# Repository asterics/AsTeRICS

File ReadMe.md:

# Welcome to AsTeRICS
-------------------

AsTeRICS is a free and Open-Source graphical construction set for assistive technologies (AT).
It allows the creation of flexible solutions for people with disabilities using a large set of sensors and actuators.

Possible applications are  
* Computer input (mouse, keyboard, joystick)
* Environmental Control (KNX, FS20, IR, EnOcean, openHAB)
* Toys and Games (Playstation 3, computer games, RC-toys ...)
* Brain/Neural computer interfaces (Enobio, OpenVIBE, OpenEEG)
* Android Phone support (SMS, calls)
* and many more!

For more information see our website http://www.asterics.eu.

## Demos (Solutions)
Check out some solutions [here](https://www.asterics.eu/solutions/)

## Quick Build Instructions
To clone and compile the AsTeRICS framework, please execute the following steps:

1. Clone Repository (submodules will be cloned during build)
  ```
  git clone https://github.com/asterics/AsTeRICS.git
  ```
2. Install the [**Java Development Kit (JDK, 32bit preferred) = 8**](http://www.oracle.com/technetwork/java/javase/downloads/index.html)
  * Ensure to set ```JAVA_HOME``` to the folder where you installed the Java JDK and add the JDK bin path to the  Environment Variable ```Path```
3. [apache ant build framework (version >= 1.9.1)](http://ant.apache.org/bindownload.cgi)
  * Ensure to set ```ANT_HOME``` to the folder where you installed ant and add the ant bin path to the Environment Variable ```Path```
  * The ```git``` command line tool must be available from within ant, ensure to set the Environment Variable ```Path``` to the respective ```bin``` folder.
4. Open a terminal and start the AsTeRICS Runtime Environment (ARE) by calling:

  ```
  ant run
  ```
  
 If you don't need commandline support, you can use an IDE for Java Developers, e.g. [Eclipse](http://www.eclipse.org/downloads/packages/eclipse-ide-java-developers/neon3), which already contains ant. There you can directly execute ant targets by selecting the build file ```build.xml``` and select the target of choice, e.g. ```run```.
 
## Documentation

* [AsTeRICS Tutorial with screencasts](https://ds.gpii.net/learn/tutorials/integration-alternative-input-modalities)
* [Getting Started](https://www.asterics.eu/get-started/)
* [Tutorials](https://www.asterics.eu/customize/)
* [Developer Manual](https://www.asterics.eu/develop/)
* [Plugin Hellp](https://www.asterics.eu/plugins/)

You can find more documentation and build plans for some hardware devices in [ModelGuides](https://github.com/asterics/AsTeRICS/tree/master/Documentation/ModelGuides) and  [DIYGuides](https://github.com/asterics/AsTeRICS/tree/master/Documentation/DIYGuides).

## Contact

If you want to contribute to the AsTeRICS project, have questions or just need help using it don't bother to create an [issue](https://github.com/asterics/AsTeRICS/issues), pull request or via the [contact page](https://www.asterics.eu/get-involved/Contact.html).  

If you want to support the development of AsTeRICS you're very welcome to donate to the AsTeRICS Foundation:

<div>

<span>&nbsp;&nbsp;&nbsp;</span>

</div>

## License

This project has been partly funded by the European Commission,  Grant Agreement Number 247730 in the years 2010-2012.
Since 2013, further development of AsTeRICS software and hardware components is hosted at:  https://github.com/asterics/AsTeRICS

#### ACS and NativeASAPI libraries
Licensed under [LGPL](http://www.gnu.org/licenses/lgpl.html)

#### ARE-middleware, ARE-plugins, services and BNCI Suite
Licensed under a dual license [MIT or GPL with CLASSPATH exception](ARE-LICENSE_MITOrGPLv3WithException.txt)

##### How to apply the dual licensing

You may use these components under the terms of the MIT License, if no source code (plugins, services, libraries, ...) which is contained in your desired collection of ARE plugins and services is licensed under the GNU General Public License (GPL).
In order for that, you can remove unneeded plugins or services.

**Please note:** There are also some plugins (e.g. MathEvaluator, VLC) which are **GPL without CLASSPATH** exception, so in this case your license would have to be **GPL** as well.

Please have a look at the individual licenses of the AsTeRICS plugins and services. You find the license files in the subfolder LICENSE of every plugin.

## Disclaimer

This software is provided 'as-is', without any express or implied warranty. 
In no event will the authors be held liable for any damages arising from the use of this software. See [DISCLAIMER](DISCLAIMER.TXT)

## Releases

* See [CHANGELOG](./CHANGELOG.md) or old [Release Notes](RELEASE_NOTES.md) and the published [releases](https://github.com/asterics/AsTeRICS/releases)

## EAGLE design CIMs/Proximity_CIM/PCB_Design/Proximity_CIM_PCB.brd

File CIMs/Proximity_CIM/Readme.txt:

AsTeRICS proximity CIM, FHTW

The firmware fits for the Atmel AVR AT90USB1286 microcontroller 
(e.g. mounted on the "teensy++" board, see http://www.pjrc.com/store/teensypp.html)

The proximity CIM provides a distance measurement curcuit based upun a CNY-70 infrared object detection sensor.
It can be used a assistive input device for persons to select / control via small movement e.g. of a finger or of the chin.

Important files/folders:
  ProximityCIM.aps:  project file, can be opened/built with AVRStudio 4 + WinAVR
  ProximityCIM.hex:  binary/executable, can be downloaded via Atmel FLIP into the microcontroller
  subfolder "PCB_Design": schematics/layout files for a PCB conaining microcontroller and circuits for the proximity detetor

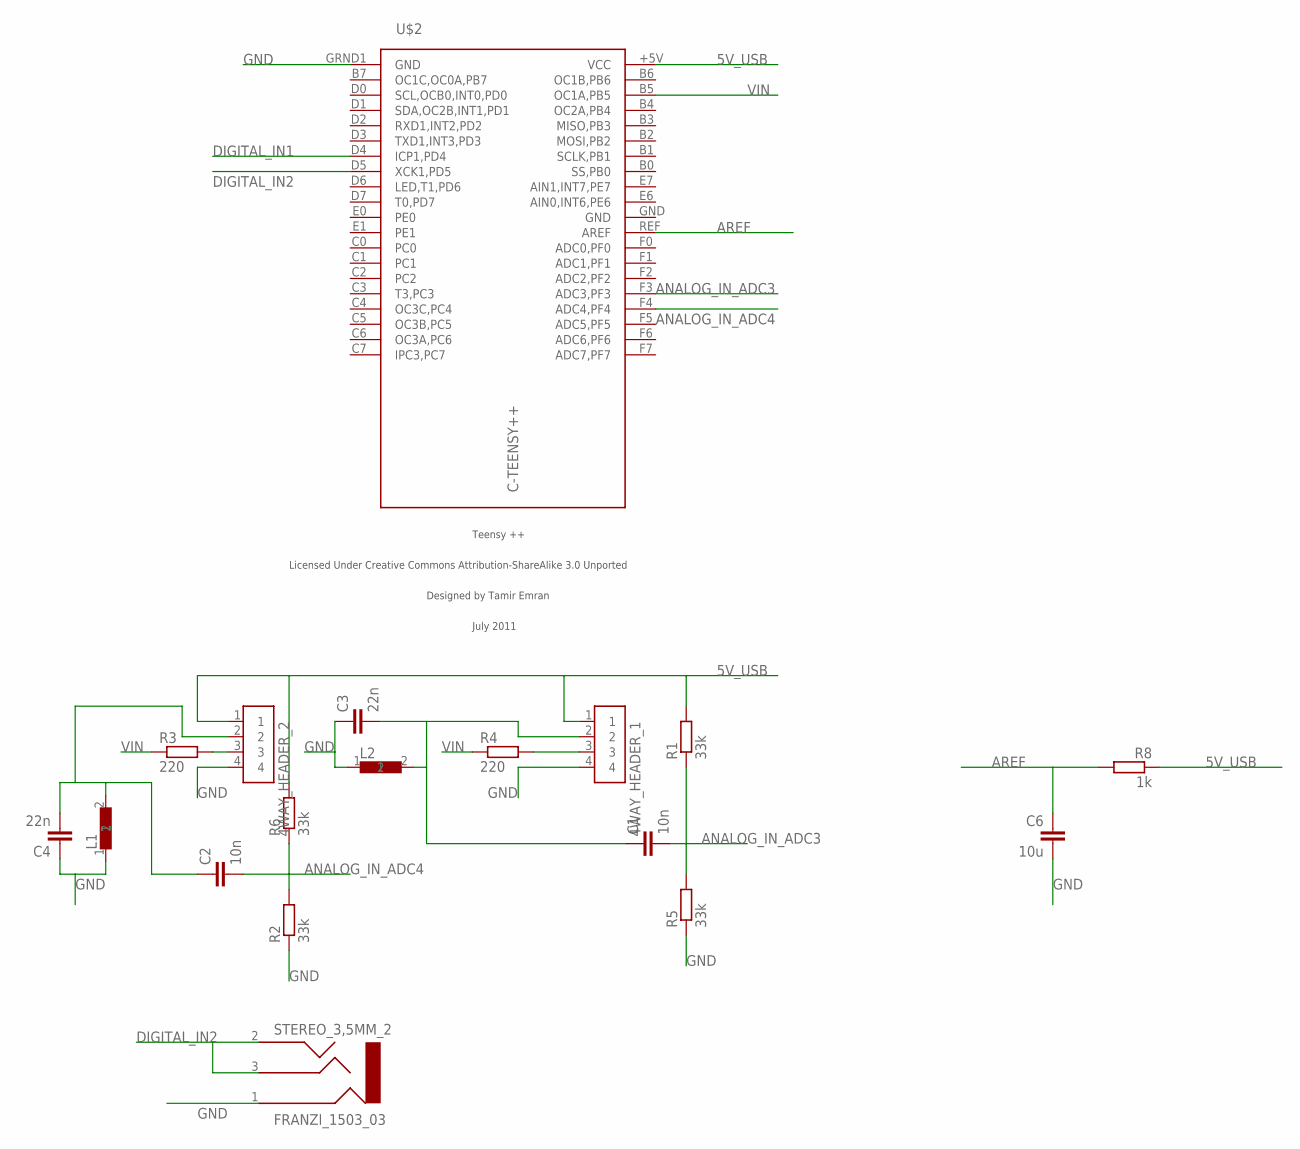
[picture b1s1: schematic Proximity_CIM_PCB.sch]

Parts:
4WAY_HEADER_1, 4WAY_HEADER_2: 4WAY_HEADER
C1, C2: 10n; C0805
C3, C4: 22n; C1206
C6: 10u; C0805
L1, L2: INDUCTOR_1
R1, R2, R5, R6: 33k; R0805
R3, R4: 220; R0805
R8: 1k; R0805
STEREO_3,5MM_2: FRANZI_1503_03; 1503_03
U$2: C-TEENSY++; TEENSY++

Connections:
5V_USB: 4WAY_HEADER_1.1, 4WAY_HEADER_2.1, R1.2, R6.2, R8.1, U$2.+5V (VCC)
ANALOG_IN_ADC3: C1.2, R1.1, R5.2, U$2.F3 (ADC3,PF3)
ANALOG_IN_ADC4: C2.2, R2.2, R6.1, U$2.F4 (ADC4,PF4)
AREF: C6.1, R8.2, U$2.REF (AREF)
DIGITAL_IN1: U$2.D4 (ICP1,PD4)
DIGITAL_IN2: STEREO_3,5MM_2.2, STEREO_3,5MM_2.3, U$2.D5 (XCK1,PD5)
GND: 4WAY_HEADER_1.4, 4WAY_HEADER_2.4, C3.1, C4.1, C6.2, L1.1, L2.1, R2.1, R5.1, STEREO_3,5MM_2.1, U$2.GND, U$2.GRND1 (GND)
unnamed: 4WAY_HEADER_1.3, R4.2
unnamed: 4WAY_HEADER_1.2, C1.1, C3.2, L2.2
unnamed: 4WAY_HEADER_2.2, C2.1, C4.2, L1.2
unnamed: 4WAY_HEADER_2.3, R3.2
VIN: R3.1, R4.1, U$2.B5 (OC1A,PB5)

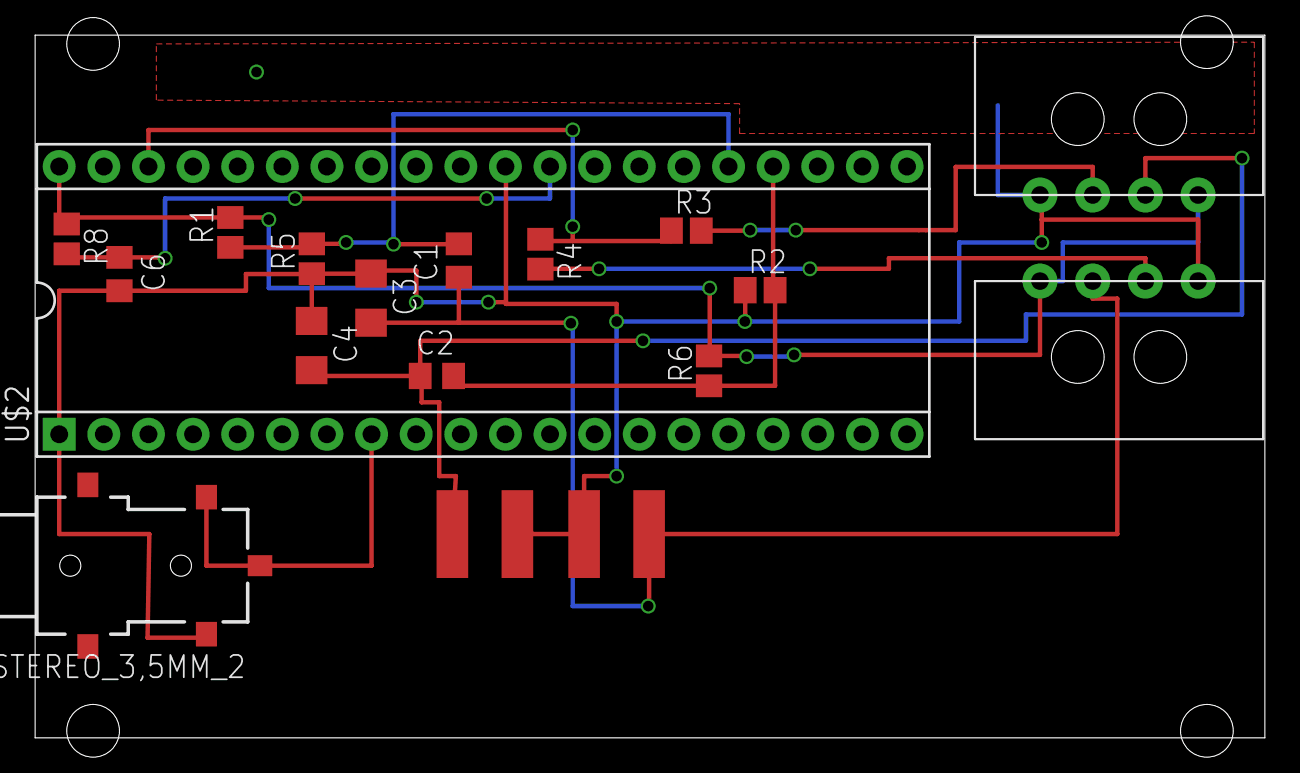
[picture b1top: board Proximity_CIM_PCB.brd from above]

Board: 2 copper layers, 70.0 x 40.0 mm, 18 parts (0 on the bottom side), 11 nets.

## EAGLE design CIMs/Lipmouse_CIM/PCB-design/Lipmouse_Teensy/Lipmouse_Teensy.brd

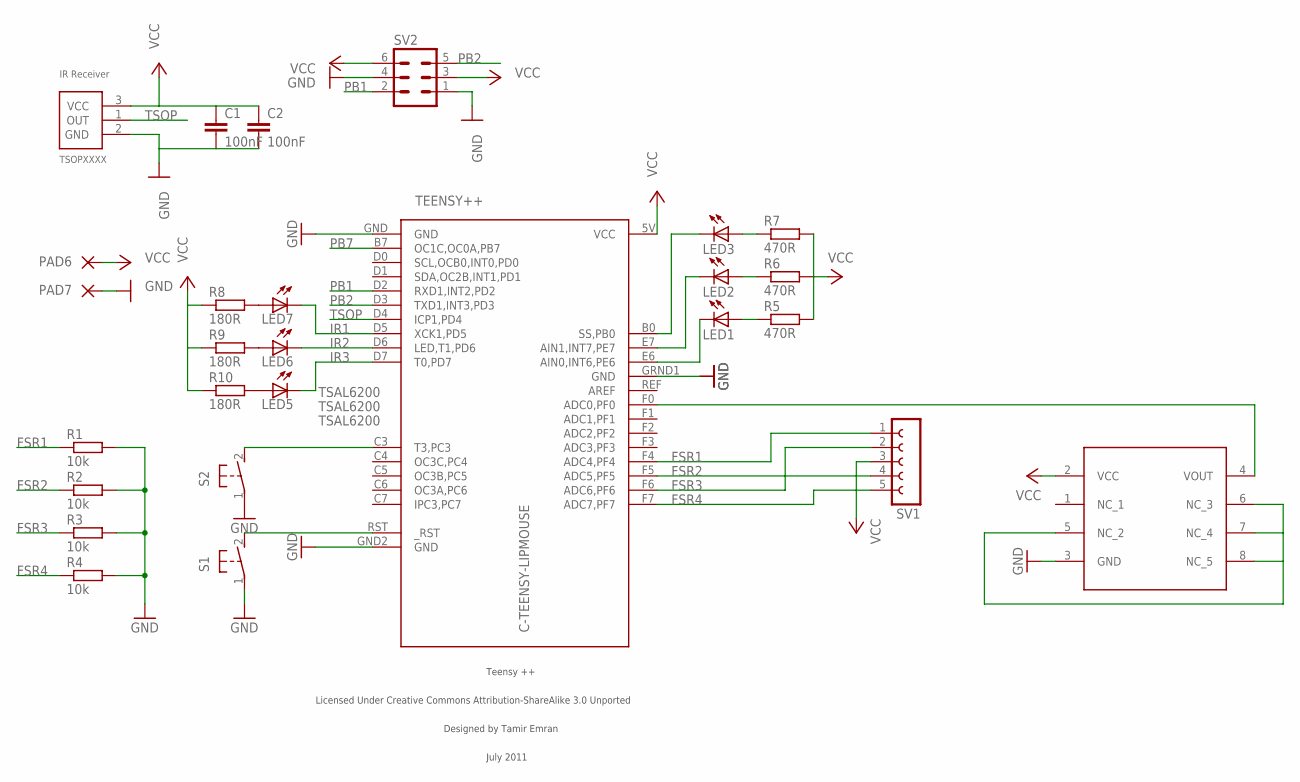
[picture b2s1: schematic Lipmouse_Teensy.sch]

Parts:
C1, C2: 100nF; C0805K
LED1, LED2, LED3: LED3MM
LED5, LED6, LED7: TSAL6200; LED5MM
PAD6, PAD7: 1,6/0,9
R1, R2, R3, R4: 10k; R0805W
R5, R6, R7: 470R; R0805W
R8, R9, R10: 180R; R0805W
S1, S2: 31-XX; B3F-31XX
SV1: FE05-1
SV2: ML6
TEENSY++: C-TEENSY-LIPMOUSE; TEENSY++
U$2: MP3V7007GP; SMP_MP3V7007
U$3: TSOP4838; TSOP2XXX

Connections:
FSR1: R1.1, SV1.1, TEENSY++.F4 (ADC4,PF4)
FSR2: R2.1, SV1.4, TEENSY++.F5 (ADC5,PF5)
FSR3: R3.1, SV1.2, TEENSY++.F6 (ADC6,PF6)
FSR4: R4.1, SV1.5, TEENSY++.F7 (ADC7,PF7)
GND: C1.2, C2.2, PAD7.1, R1.2, R2.2, R3.2, R4.2, S1.1, S2.1, SV2.1, SV2.4, TEENSY++.GND, TEENSY++.GND2 (GND), TEENSY++.GRND1 (GND), U$2.3 (GND), U$3.2 (GND)
IR1: LED7.K (C), TEENSY++.D5 (XCK1,PD5)
IR2: LED6.K (C), TEENSY++.D6 (LED,T1,PD6)
IR3: LED5.K (C), TEENSY++.D7 (T0,PD7)
unnamed: LED1.A, R5.1
unnamed: LED2.A, R6.1
unnamed: LED3.A, R7.1
unnamed: S2.2 (S), TEENSY++.C3 (T3,PC3)
unnamed: LED1.K (C), TEENSY++.E6 (AIN0,INT6,PE6)
unnamed: TEENSY++.F0 (ADC0,PF0), U$2.4 (VOUT)
unnamed: LED2.K (C), TEENSY++.E7 (AIN1,INT7,PE7)
unnamed: LED3.K (C), TEENSY++.B0 (SS,PB0)
unnamed: LED7.A, R8.2
unnamed: LED6.A, R9.2
unnamed: LED5.A, R10.2
unnamed: U$2.5 (NC_2), U$2.6 (NC_3), U$2.7 (NC_4), U$2.8 (NC_5)
unnamed: S1.2 (S), TEENSY++.RST (_RST)
PB1: SV2.2, TEENSY++.D2 (RXD1,INT2,PD2)
PB2: SV2.5, TEENSY++.D3 (TXD1,INT3,PD3)
PB7: TEENSY++.B7 (OC1C,OC0A,PB7)
TSOP: TEENSY++.D4 (ICP1,PD4), U$3.1 (OUT)
VCC: C1.1, C2.1, PAD6.1, R5.2, R6.2, R7.2, R8.1, R9.1, R10.1, SV1.3, SV2.3, SV2.6, TEENSY++.5V (VCC), U$2.2 (VCC), U$3.3 (VCC)

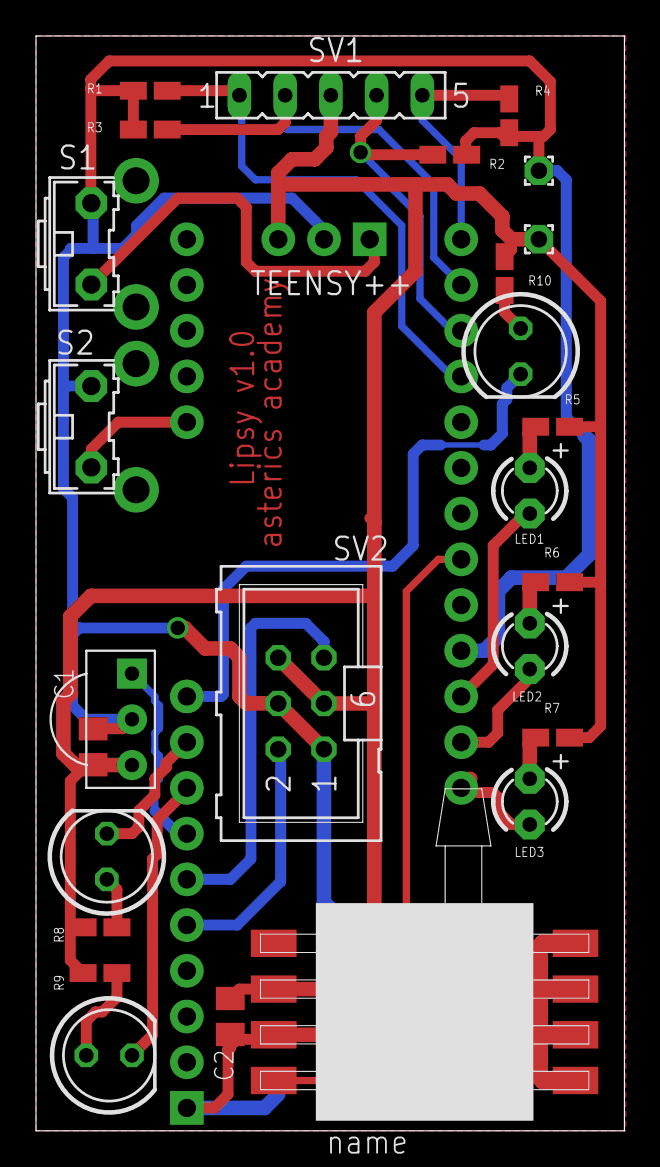
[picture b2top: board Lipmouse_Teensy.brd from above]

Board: 2 copper layers, 32.7 x 60.8 mm, 27 parts (1 on the bottom side), 25 nets.

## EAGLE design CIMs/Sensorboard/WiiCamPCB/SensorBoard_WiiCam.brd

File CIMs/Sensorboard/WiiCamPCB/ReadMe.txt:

AsTeRICs Sensorboard Printed Circuit Board design files

This folder contains the EageCad Design Files for the Sensorboard - version which supports the Optical Sensor of the Wiimote (via I2C interface)
Please refer to the SmartVisionModule DIY guide (documentation/DIYGuides/SmartVisionModule) for more details.

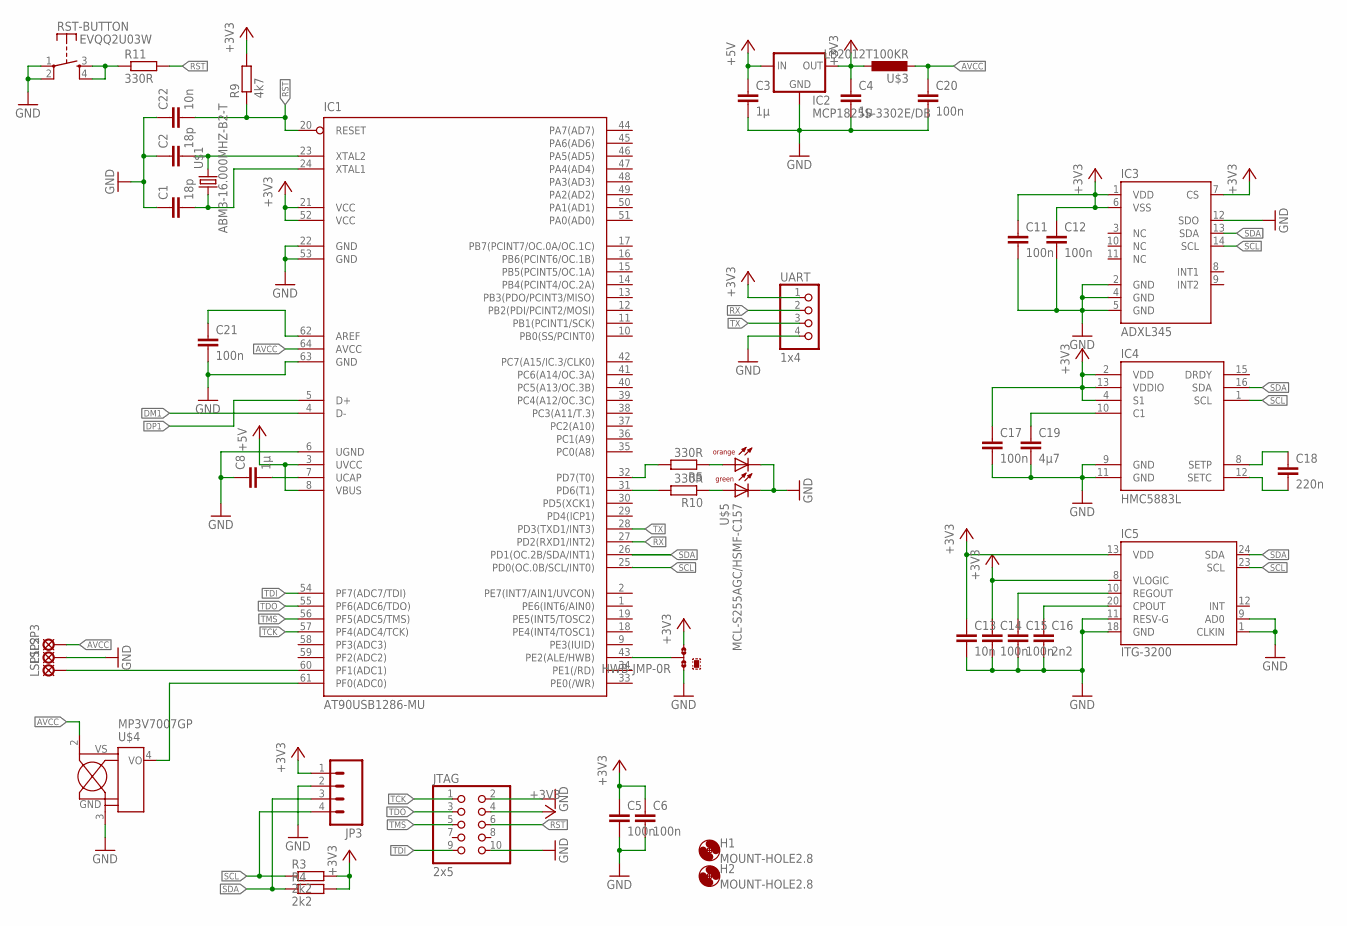
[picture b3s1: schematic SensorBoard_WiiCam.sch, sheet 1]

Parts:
C1, C2: 18p; C0603K
C3, C4, C8: 1µ; C0603K
C5, C6, C11, C12, C14, C15, C17, C20, C21: 100n; C0603K
C13, C22: 10n; C0603K
C16: 2n2; C0603K
C18: 220n; C0603K
C19: 4µ7; C0603K
H1, H2: MOUNT-HOLE2.8; 2,8
HWB-JMP: 0R-JUMPB; B0R-JMP
IC1: AT90USB1286-MU; TQFP64
IC2: MCP1825S-3302E/DB; SOT223
IC3: ADXL345; LGA14
IC4: HMC5883L; LPCC16
IC5: ITG-3200; QFN-24
JP3: M04PTH; 1X04
JTAG: 2x5; 2X05
LSP1, LSP2, LSP3: NC; SE14
R3, R4: 2k2; R0603
R5, R10, R11: 330R; R0603
R9: 4k7; R0603
RST-BUTTON: EVQQ2U03W; EVQQ2
U$1: ABM3-16.000MHZ-B2-T; SMD_5X3.2MM
U$3: LB2012T100KR; L-2012
U$4: MP3V7007GP; SOP-8
U$5: MCL-S255AGC/HSMF-C157; DUOLED-1210
UART: 1x4; 1X04

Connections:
+3V3: C4.1, C5.1, C6.1, C11.1, C12.1, C13.1, C14.1, C17.1, HWB-JMP.3, IC1.21 (VCC), IC1.52 (VCC), IC2.3 (OUT), IC3.1 (VDD), IC3.6 (VSS), IC3.7 (CS), IC4.2 (VDD), IC4.4 (S1), IC4.13 (VDDIO), IC5.8 (VLOGIC), IC5.13 (VDD), JP3.1, JTAG.4, R3.2, R4.2, R9.2, U$3.1, UART.1; also elsewhere on the board
+5V: C3.1, IC1.3 (UVCC), IC1.8 (VBUS), IC2.1 (IN); also elsewhere on the board
AVCC: C20.1, IC1.64 (AVCC), LSP3.MP, U$3.2, U$4.2 (VS)
DM1: IC1.4 (D-); also elsewhere on the board
DP1: IC1.5 (D+); also elsewhere on the board
GND: C1.1, C2.1, C3.2, C4.2, C5.2, C6.2, C8.1, C11.2, C12.2, C13.2, C14.2, C15.2, C16.2, C17.2, C19.2, C20.2, C21.2, C22.1, HWB-JMP.1, IC1.6 (UGND), IC1.22 (GND), IC1.53 (GND), IC1.63 (GND), IC2.2 (GND), IC2.4 (GND), IC3.2 (GND), IC3.4 (GND), IC3.5 (GND), IC3.12 (SDO), IC4.9 (GND), IC4.11 (GND), IC5.1 (CLKIN), IC5.9 (AD0), IC5.11 (RESV-G), IC5.18 (GND), JP3.2, JTAG.2, JTAG.10, LSP2.MP, RST-BUTTON.1, RST-BUTTON.2, U$4.3 (GND), U$5.1 (C), U$5.2 (C), UART.4; also elsewhere on the board
unnamed: C1.2, IC1.24 (XTAL1), U$1.P$1 (1)
unnamed: C2.2, IC1.23 (XTAL2), U$1.P$2 (2)
unnamed: C8.2, IC1.7 (UCAP)
unnamed: C16.1, IC5.20 (CPOUT)
unnamed: C18.1, IC4.8 (SETP)
unnamed: C15.1, IC5.10 (REGOUT)
unnamed: C18.2, IC4.12 (SETC)
unnamed: R5.1, U$5.4 (AO)
unnamed: C19.1, IC4.10 (C1)
unnamed: C21.1, IC1.62 (AREF)
unnamed: HWB-JMP.2, IC1.43 (PE2(ALE/HWB))
unnamed: IC1.31 (PD6(T1)), R10.2
unnamed: R10.1, U$5.3 (AG)
unnamed: IC1.32 (PD7(T0)), R5.2
unnamed: R11.1, RST-BUTTON.3 (S), RST-BUTTON.4 (S)
unnamed: IC1.61 (PF0(ADC0)), U$4.4 (OUT)
unnamed: IC1.60 (PF1(ADC1)), LSP1.MP
RST: C22.2, IC1.20 (RESET), JTAG.6, R9.1, R11.2
RX: IC1.27 (PD2(RXD1/INT2)), UART.2
SCL: IC1.25 (PD0(OC.0B/SCL/INT0)), IC3.14 (SCL), IC4.1 (SCL), IC5.23 (SCL), JP3.4, R3.1
SDA: IC1.26 (PD1(OC.2B/SDA/INT1)), IC3.13 (SDA), IC4.16 (SDA), IC5.24 (SDA), JP3.3, R4.1
TCK: IC1.57 (PF4(ADC4/TCK)), JTAG.1
TDI: IC1.54 (PF7(ADC7/TDI)), JTAG.9
TDO: IC1.55 (PF6(ADC6/TDO)), JTAG.3
TMS: IC1.56 (PF5(ADC5/TMS)), JTAG.5
TX: IC1.28 (PD3(TXD1/INT3)), UART.3

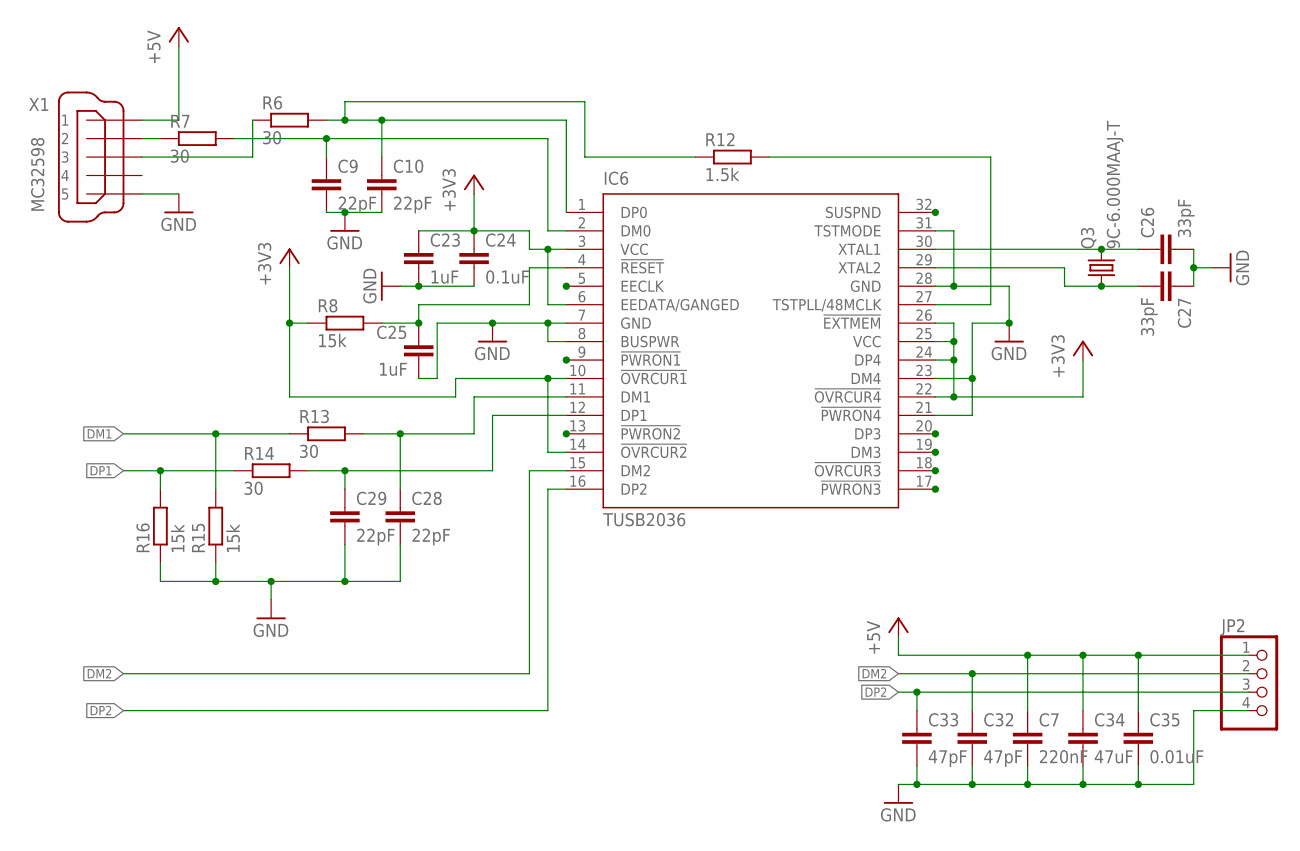
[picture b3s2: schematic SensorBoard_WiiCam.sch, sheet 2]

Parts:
C7: 220nF; C0603
C9, C10, C28, C29: 22pF; C0603
C23, C25: 1uF; C0603
C24: 0.1uF; C0603
C26, C27: 33pF; C0603
C32, C33: 47pF; C0603
C34: 47uF; C0805
C35: 0.01uF; C0603
IC6: TUSB2036; VF_S-PQFP-G32
JP2: PINHD-1X4; 1X04
Q3: 9C-6.000MAAJ-T; CSM-7X-DU
R6, R7, R13, R14: 30; R0603
R8, R15, R16: 15k; R0603
R12: 1.5k; R0603
X1: MC32598; 32005-201

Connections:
+3V3: C23.1, C24.1, IC6.3 (VCC), IC6.6 (EEDATA/GANGED), IC6.10 (!OVRCUR1), IC6.14 (!OVRCUR2), IC6.22 (!OVRCUR4), IC6.24 (DP4), IC6.25 (VCC), IC6.26 (!EXTMEM), R8.1; also elsewhere on the board
+5V: C7.1, C34.1, C35.1, JP2.1, X1.1; also elsewhere on the board
DM1: R13.1, R15.2; also elsewhere on the board
DM2: C32.1, IC6.15 (DM2), JP2.2
DP1: R14.1, R16.2; also elsewhere on the board
DP2: C33.1, IC6.16 (DP2), JP2.3
GND: C7.2, C9.2, C10.2, C23.2, C24.2, C25.2, C26.2, C27.1, C28.2, C29.2, C32.2, C33.2, C34.2, C35.2, IC6.7 (GND), IC6.8 (BUSPWR), IC6.21 (!PWRON4), IC6.23 (DM4), IC6.28 (GND), IC6.31 (TSTMODE), JP2.4, R15.1, R16.1, X1.5; also elsewhere on the board
unnamed: C9.1, IC6.2 (DM0), R7.2
unnamed: R7.1, X1.2
unnamed: R6.1, X1.3
unnamed: C10.1, IC6.1 (DP0), R6.2, R12.1
unnamed: C25.1, IC6.4 (!RESET), R8.2
unnamed: C26.1, IC6.30 (XTAL1), Q3.2
unnamed: C27.2, IC6.29 (XTAL2), Q3.1
unnamed: IC6.27 (TSTPLL/48MCLK), R12.2
unnamed: C28.1, IC6.11 (DM1), R13.2
unnamed: C29.1, IC6.12 (DP1), R14.2

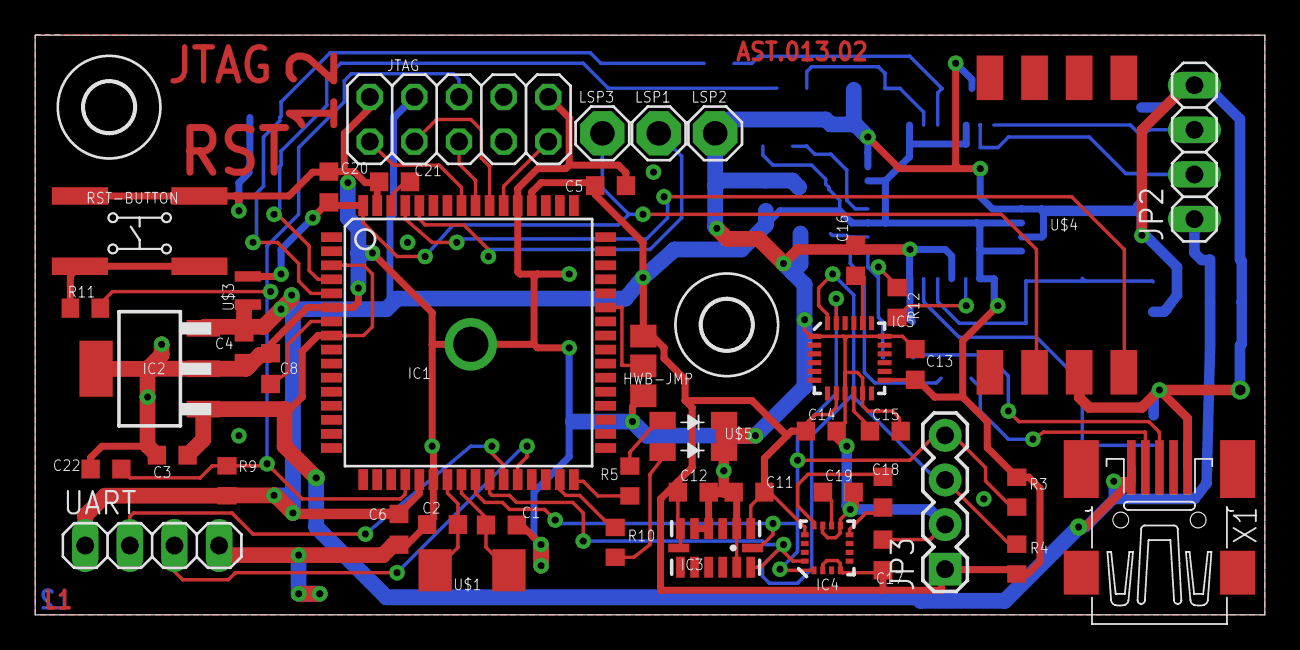
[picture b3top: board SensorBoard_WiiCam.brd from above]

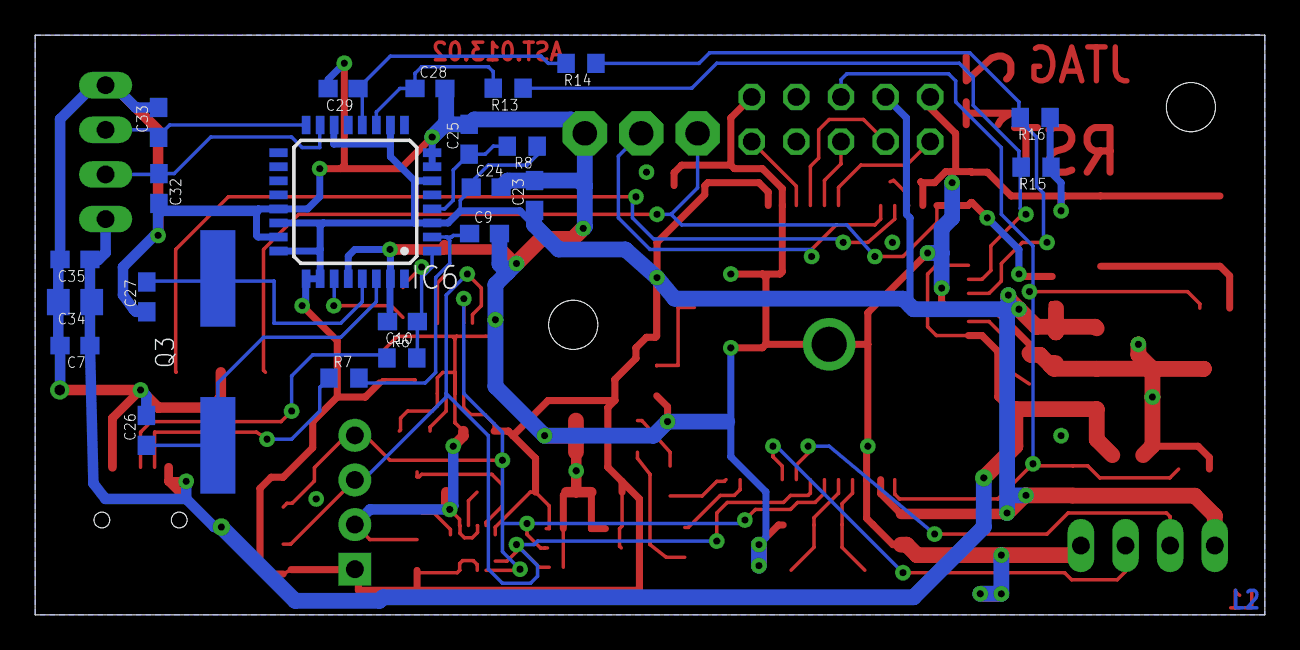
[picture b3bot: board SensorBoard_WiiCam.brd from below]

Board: 2 copper layers, 70.0 x 33.0 mm, 70 parts (23 on the bottom side), 44 nets.

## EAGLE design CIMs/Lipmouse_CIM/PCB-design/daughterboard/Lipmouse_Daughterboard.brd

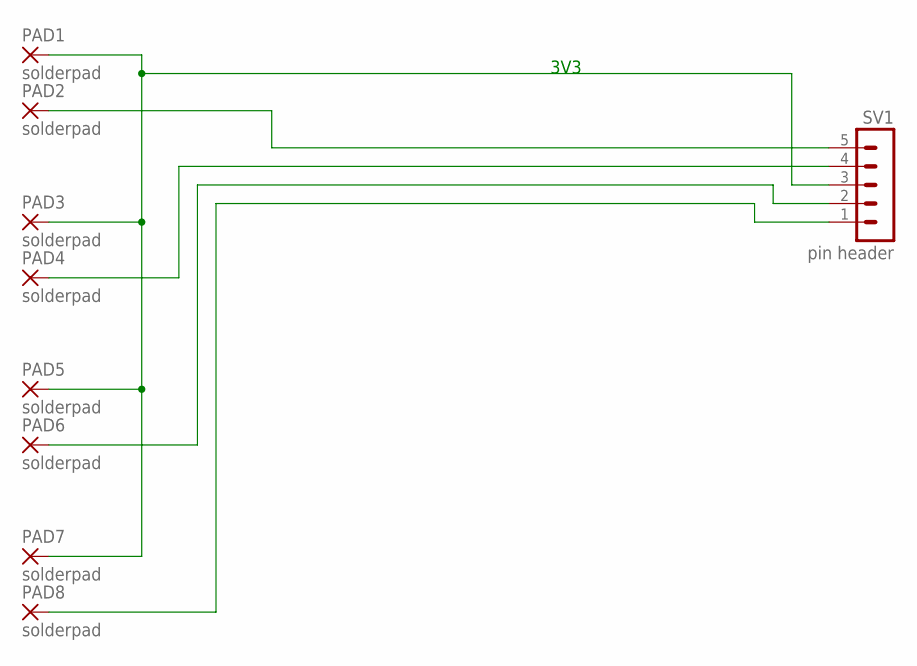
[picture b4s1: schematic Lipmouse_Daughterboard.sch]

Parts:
PAD1, PAD2, PAD3, PAD4, PAD5, PAD6, PAD7, PAD8: solderpad; SMD2,54-5,08
SV1: pin header; MA05-1

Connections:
3V3: PAD1.1, PAD3.1, PAD5.1, PAD7.1, SV1.3
unnamed: PAD2.1, SV1.5
unnamed: PAD4.1, SV1.4
unnamed: PAD6.1, SV1.2
unnamed: PAD8.1, SV1.1

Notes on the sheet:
3V3

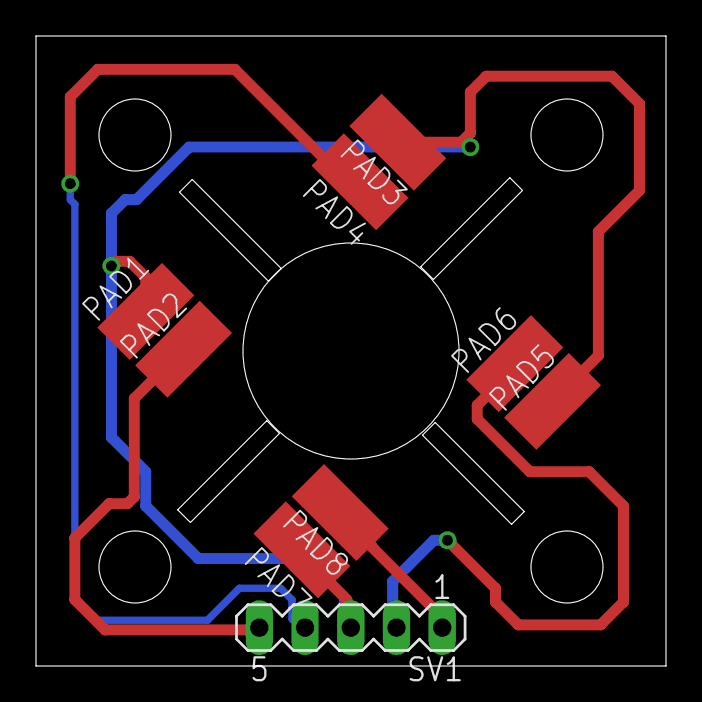
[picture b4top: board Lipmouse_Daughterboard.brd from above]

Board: 2 copper layers, 35.0 x 35.0 mm, 9 parts (0 on the bottom side), 5 nets.

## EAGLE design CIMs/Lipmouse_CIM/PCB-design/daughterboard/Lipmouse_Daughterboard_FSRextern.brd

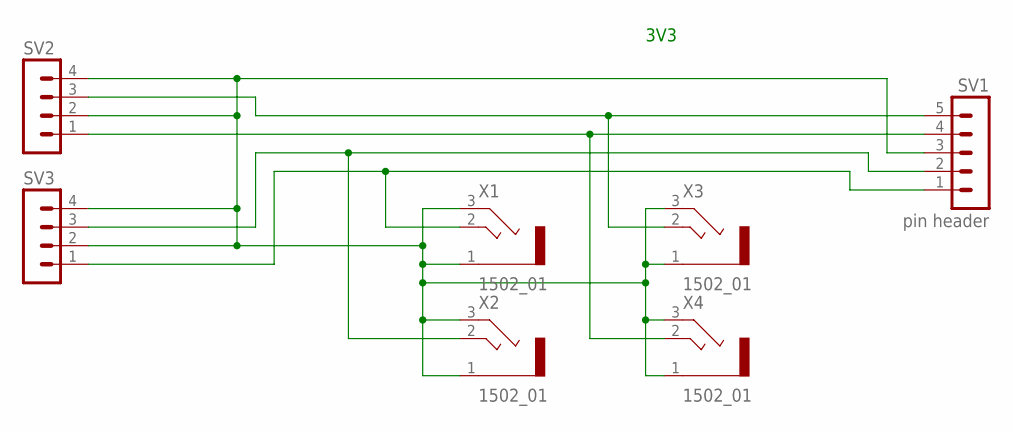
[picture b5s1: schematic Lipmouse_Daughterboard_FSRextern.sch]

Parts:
SV1: pin header; MA05-1
SV2, SV3: MA04-1
X1, X2, X3, X4: 1502_01

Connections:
3V3: SV1.3, SV2.2, SV2.4, SV3.2, SV3.4, X1.1, X1.3 (2), X2.1, X2.3 (2), X3.1, X3.3 (2), X4.1, X4.3 (2)
unnamed: SV1.4, SV2.1, X4.2 (3)
unnamed: SV1.5, SV2.3, X3.2 (3)
unnamed: SV1.2, SV3.3, X2.2 (3)
unnamed: SV1.1, SV3.1, X1.2 (3)

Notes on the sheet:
3V3

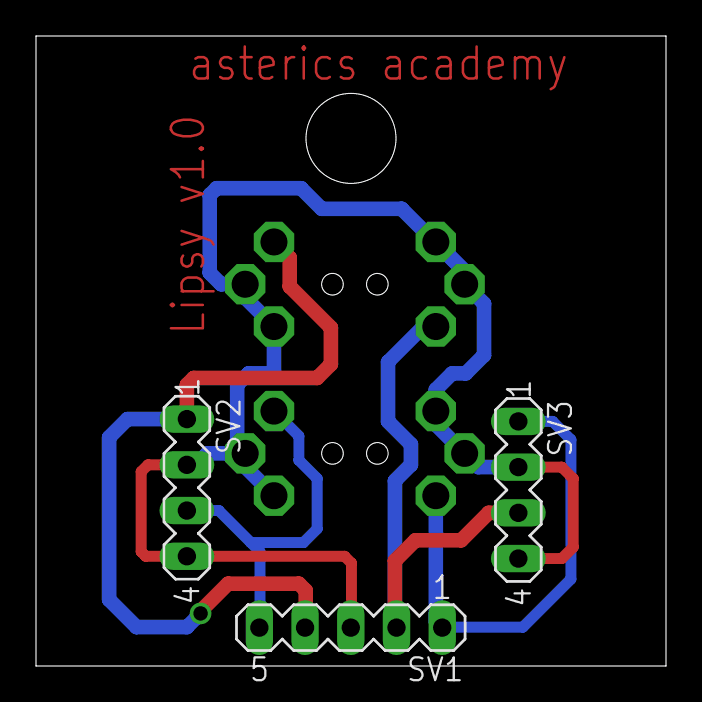
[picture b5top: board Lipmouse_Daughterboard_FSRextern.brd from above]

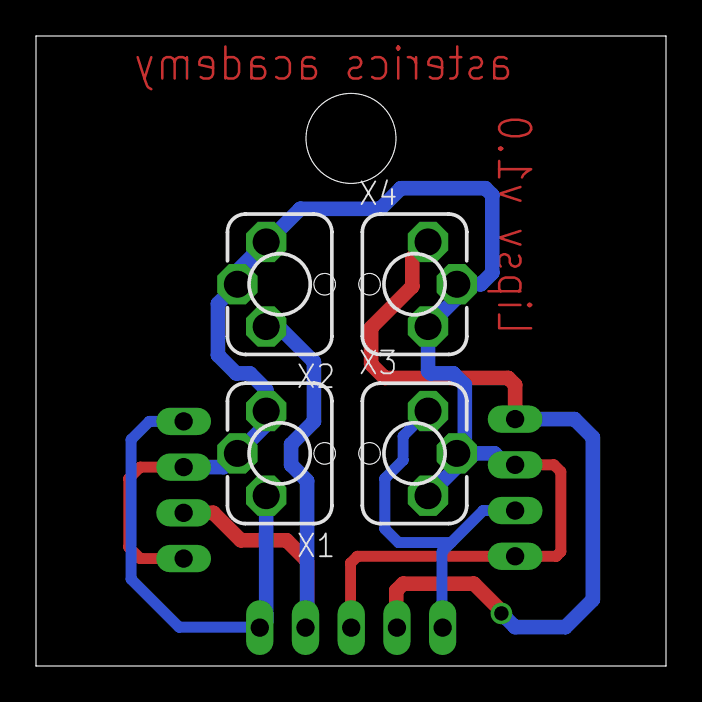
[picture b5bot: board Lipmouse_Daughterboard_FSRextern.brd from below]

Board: 2 copper layers, 35.0 x 35.0 mm, 7 parts (4 on the bottom side), 5 nets.

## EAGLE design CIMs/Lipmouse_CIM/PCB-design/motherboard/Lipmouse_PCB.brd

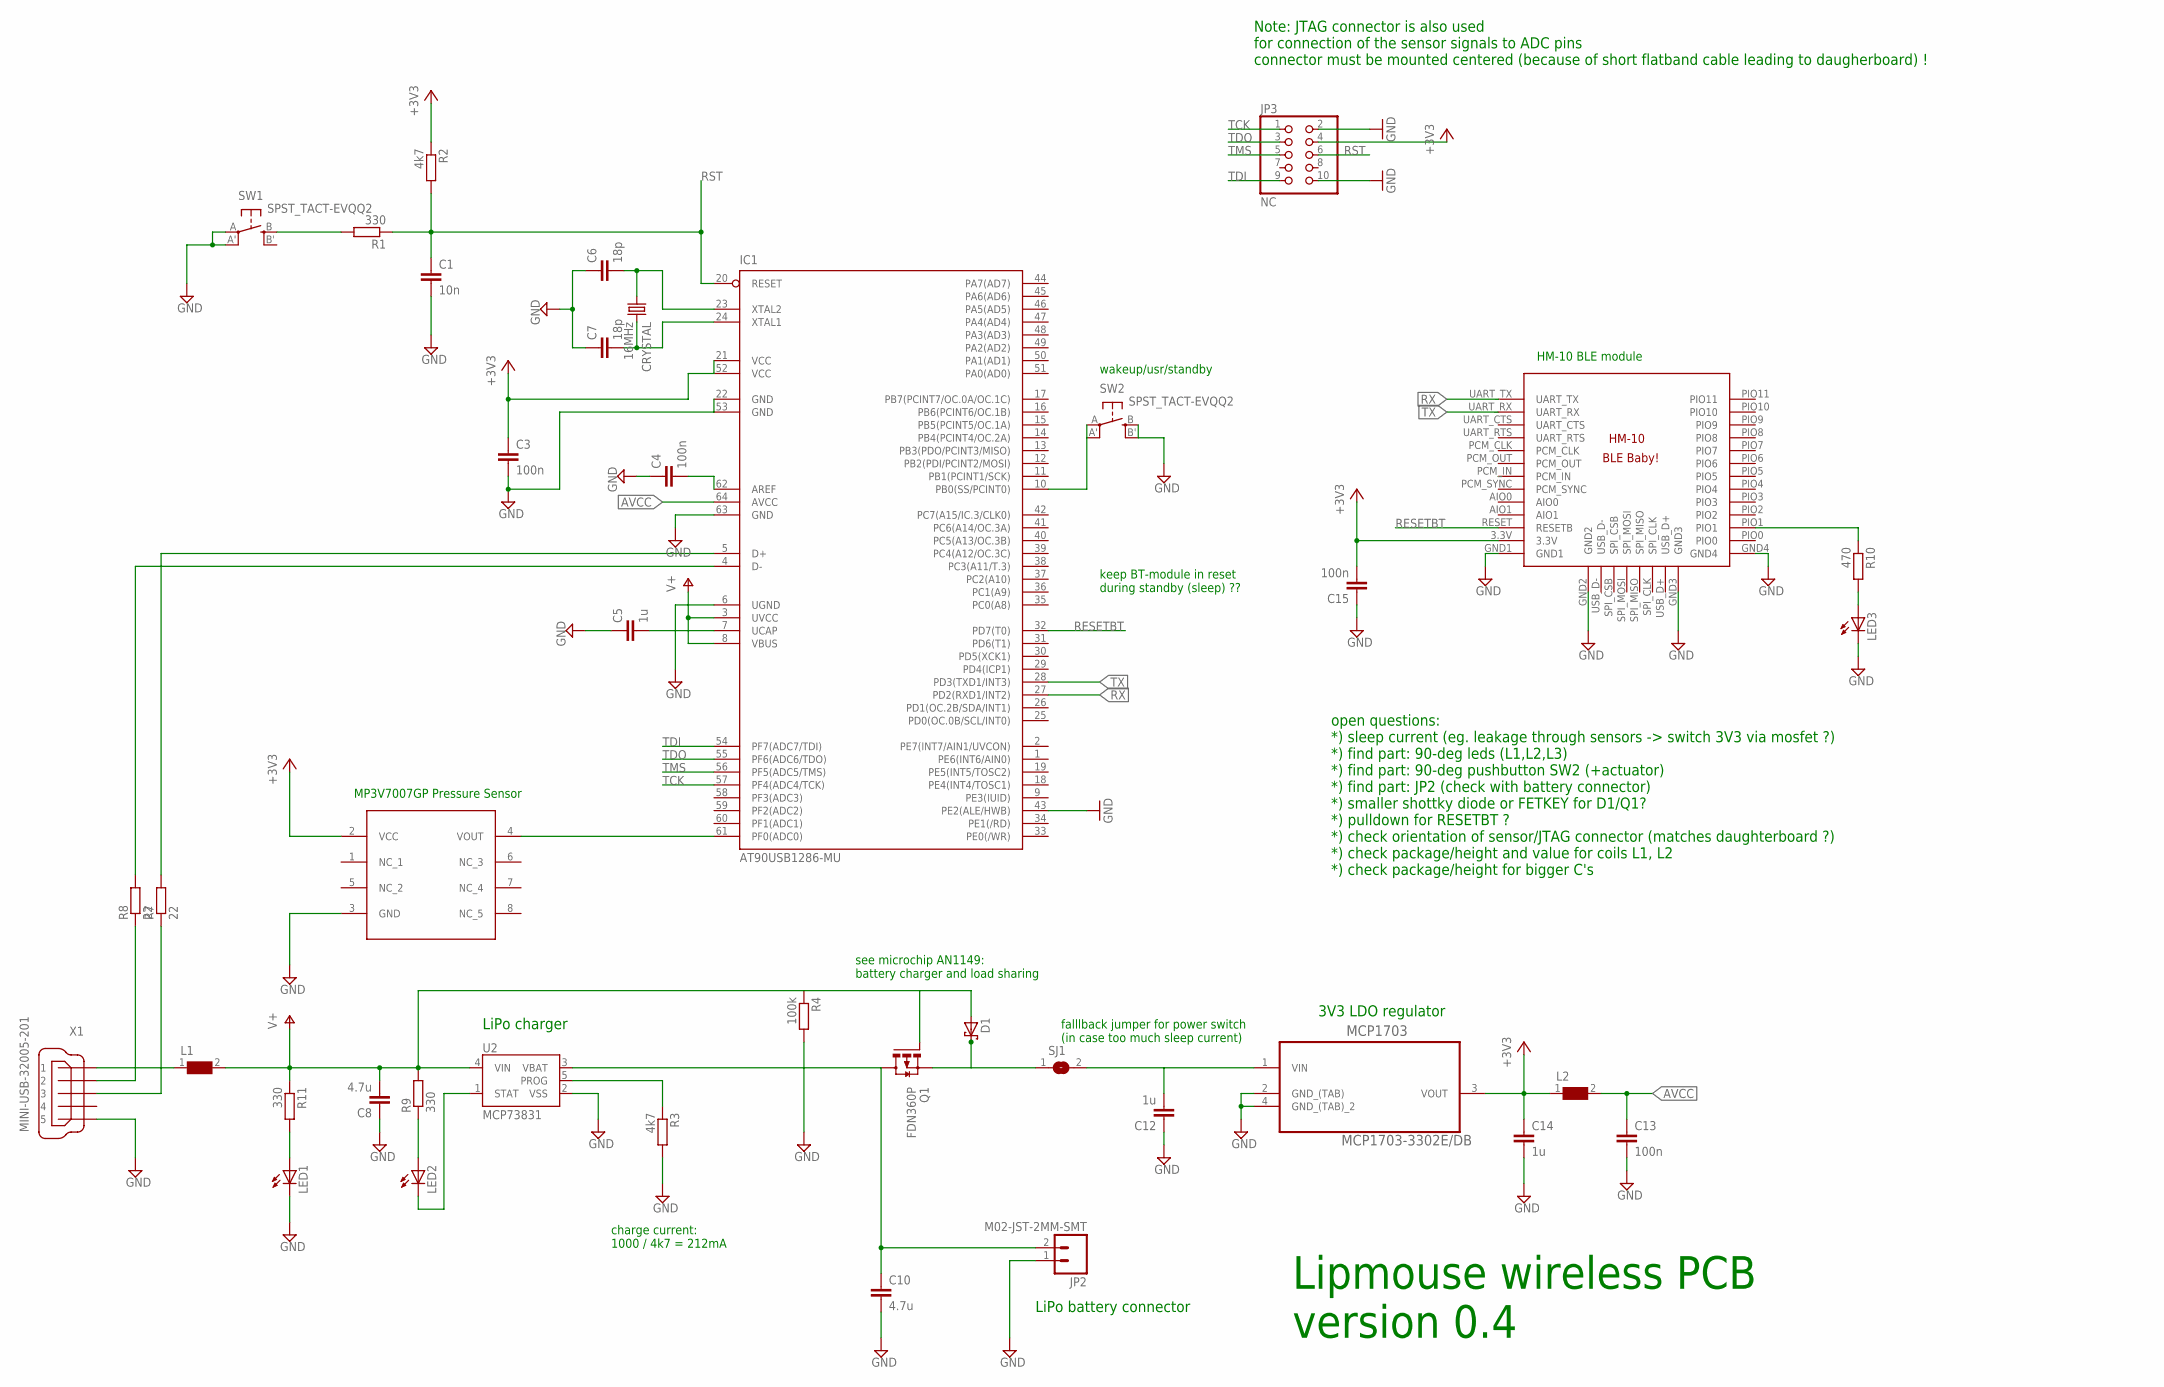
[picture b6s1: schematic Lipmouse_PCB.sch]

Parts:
C1: 10n; C0603
C3, C4, C13, C15: 100n; C0603
C5, C12, C14: 1u; C0603
C6, C7: 18p; C0603
C8, C10: 4.7u; C0805
CRYSTAL: 16MHz; CRYSTAL-TXC-7A
D1: SCHOTTKY-DIODE; DIODE_SMB
IC1: AT90USB1286-MU; TQFP64
JP2: M02-JST-2MM-SMT; JST-2-SMD
JP3: NC; 2X05
L1, L2: WE-CBF-74279201_0805; 0805
LED1, LED2, LED3: LEDSMT1206; 1206
MCP1703: MCP1703-3302E/DB; SOT230P700X180-4N
MP3V7007: MP3V7007GP; SMP_MP3V7007
Q1: FDN360P; SUPER-SOT3
R1, R9, R11: 330; R0603
R2, R3: 4k7; R0603
R4: 100k; R0603
R7, R8: 22; R0603
R10: 470; R0603
SJ1: SJ
SW1, SW2: SPST_TACT-EVQQ2; EVQ-Q2
U2: MCP73831; SOT23-5
U$1: BLE-HM-10
X1: MINI-USB-32005-201; 32005-201

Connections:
+3V3: C3.1, C14.1, C15.2, IC1.21 (VCC), IC1.52 (VCC), JP3.4, L2.1, MCP1703.3 (VOUT), MP3V7007.2 (VCC), R2.1, U$1.3.3V
AVCC: C13.1, IC1.64 (AVCC), L2.2
D+: R7.1, X1.3
D-: R8.1, X1.2
GND: C1.2, C3.2, C4.1, C5.1, C6.1, C7.1, C8.1, C10.2, C12.1, C13.2, C14.2, C15.1, IC1.6 (UGND), IC1.22 (GND), IC1.43 (PE2(ALE/HWB)), IC1.53 (GND), IC1.63 (GND), JP2.1 (2), JP3.2, JP3.10, LED1.C, LED3.C, MCP1703.2 (GND_(TAB)), MCP1703.4 (GND_(TAB)_2), MP3V7007.3 (GND), R3.2, R4.2, SW1.A, SW1.A' (P1), SW2.B (S), SW2.B' (S1), U2.2 (VSS), U$1.GND1, U$1.GND2, U$1.GND3, U$1.GND4, X1.5
unnamed: L1.1, X1.1
unnamed: LED2.C, U2.1 (STAT)
unnamed: C4.2, IC1.62 (AREF)
unnamed: C5.2, IC1.7 (UCAP)
unnamed: IC1.10 (PB0(SS/PCINT0)), SW2.A, SW2.A' (P1)
unnamed: R3.1, U2.5 (PROG)
unnamed: D1.C (A), Q1.2 (S), SJ1.1
unnamed: IC1.5 (D+), R7.2
unnamed: IC1.4 (D-), R8.2
unnamed: LED1.A, R11.2
unnamed: LED2.A, R9.1
PF0: IC1.61 (PF0(ADC0)), MP3V7007.4 (VOUT)
PIO: R10.1, U$1.PIO1
PIO1: LED3.A, R10.2
RESETBT: IC1.32 (PD7(T0)), U$1.RESET (RESETB)
RST: C1.1, IC1.20 (RESET), JP3.6, R1.1, R2.2
RX: IC1.27 (PD2(RXD1/INT2)), U$1.UART_TX
SW1: R1.2, SW1.B (S)
TCK: IC1.57 (PF4(ADC4/TCK)), JP3.1
TDI: IC1.54 (PF7(ADC7/TDI)), JP3.9
TDO: IC1.55 (PF6(ADC6/TDO)), JP3.3
TMS: IC1.56 (PF5(ADC5/TMS)), JP3.5
TX: IC1.28 (PD3(TXD1/INT3)), U$1.UART_RX
V+: C8.2, D1.A (C), IC1.3 (UVCC), IC1.8 (VBUS), L1.2, Q1.1 (G), R4.1, R9.2, R11.1, U2.4 (VIN)
VBAT: C10.1, JP2.2 (1), Q1.3 (D), U2.3 (VBAT)
VSYS: C12.2, MCP1703.1 (VIN), SJ1.2
XTAL1: C6.2, CRYSTAL.P$1 (1), IC1.23 (XTAL2)
XTAL2: C7.2, CRYSTAL.P$2 (2), IC1.24 (XTAL1)

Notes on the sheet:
MP3V7007GP Pressure Sensor
HM-10 BLE module
wakeup/usr/standby
charge current: 1000 / 4k7 = 212mA
falllback jumper for power switch (in case too much sleep current)
open questions: *) sleep current (eg. leakage through sensors -> switch 3V3 via mosfet ?) *) find part: 90-deg leds (L1,L2,L3) *) find part: 90-deg pushbutton SW2 (+actuator) *) find part: JP2 (check with battery connector) *) smaller shottky diode or FETKEY for D1/Q1? *) pulldown for RESETBT ? *) 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
see microchip AN1149: battery charger and load sharing
Lipmouse wireless PCB version 0.4
Note: JTAG connector is also used for connection of the sensor signals to ADC pins connector must be mounted centered (because of short flatband cable leading to daugherboard) !
LiPo charger
3V3 LDO regulator
LiPo battery connector
keep BT-module in reset during standby (sleep) ??

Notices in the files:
parts and their libraries:
teensy_lipmouse: Licensed Under Creative Commons Attribution-ShareAlike 3.0 Unported
SparkFun-Connectors: Licensing: Creative Commons ShareAlike 4.0 International - https://creativecommons.org/licenses/by-sa/4.0
Franzi_teensypp: Licensed Under Creative Commons
